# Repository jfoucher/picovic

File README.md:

# PICOVIC

This is a Commodore Vic-20 emulator for the [Raspberry Pi Pico](https://www.raspberrypi.org/products/raspberry-pi-pico/)

Most of the 6502 emulation code is from [fake6502](http://rubbermallet.org/fake6502.c).

A PS/2 keyboard can be plugged in to the pico according to [the schematic](hardware/picovic.pdf) and is used as an input device.

VGA output is based on the scanvideo code from [pico-extra](https://github.com/raspberrypi/pico-extras/tree/master/src/common/pico_scanvideo)

The emulation is extremely basic and for example the VIAs are only emulated so that the cursor works in BASIC. The VIC chip only has the most simple functionality, in the interest of speed and laziness. However since for the time being the emulated speed is higher than the original VIC-20, more functionality will be added in the future.

[Running BASIC video](basic.mp4)

## Hardware

I designed a PCB to go with it. You can check out the hardware folder to get the source, or [download the schematic](https://gitlab.com/jfoucher/picovic/-/jobs/artifacts/master/raw/hardware/Fabrication/Schematic.pdf?job=sch_outputs) and [gerber files](https://gitlab.com/jfoucher/picovic/-/jobs/artifacts/master/raw/hardware/Fabrication/gerbers.zip?job=pcb_outputs).

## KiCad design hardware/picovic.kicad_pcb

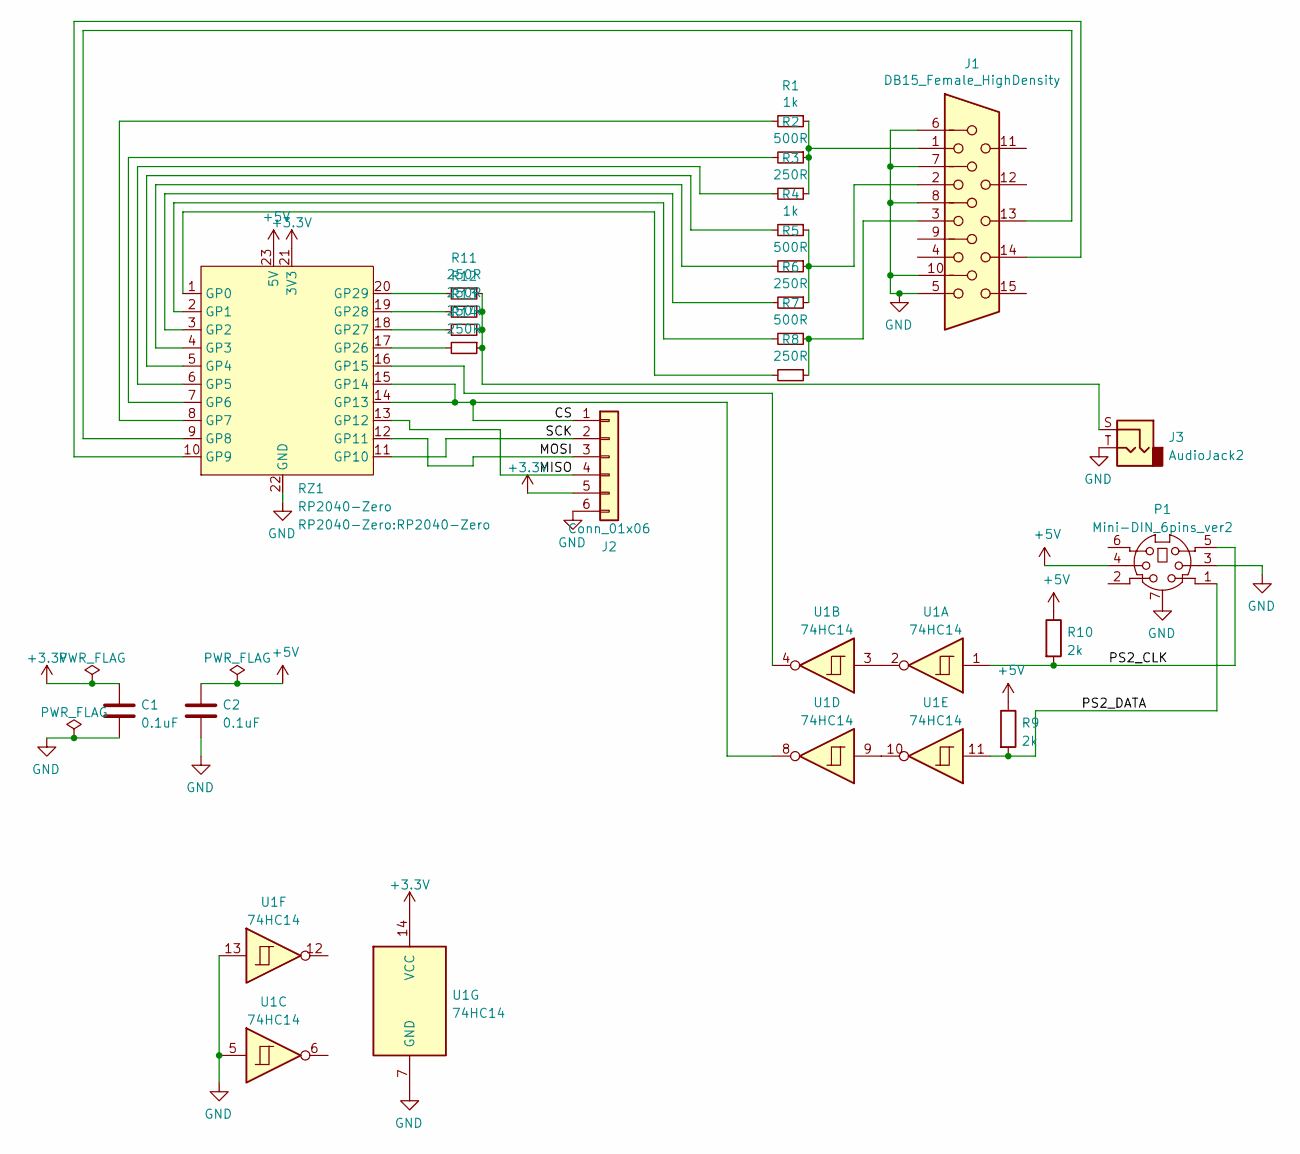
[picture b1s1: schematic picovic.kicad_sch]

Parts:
C1, C2: 0.1uF; C_Disc_D5.0mm_W2.5mm_P5.00mm
J1: DB15_Female_HighDensity; DSUB-15-HD_Female_Horizontal_P2.29x1.98mm_EdgePinOffset3.03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
J2: Conn_01x06; PinSocket_1x06_P2.54mm_Horizontal
J3: AudioJack2
P1: Mini-DIN_6pins_ver2; Connector_Mini-DIN_Female_6Pin_2rows
R1, R4: 1k; R_Axial_DIN0207_L6.3mm_D2.5mm_P7.62mm_Horizontal
R2, R5, R7: 500R; R_Axial_DIN0207_L6.3mm_D2.5mm_P7.62mm_Horizontal
R3, R6, R8, R11, R12, R13, R14: 250R; R_Axial_DIN0207_L6.3mm_D2.5mm_P7.62mm_Horizontal
R9, R10: 2k; R_Axial_DIN0207_L6.3mm_D2.5mm_P7.62mm_Horizontal
RZ1: RP2040-Zero
U1: 74HC14; DIP-14_W7.62mm_Socket

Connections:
+3.3V: C1.1, J2.5, RZ1.21 (3V3), U1.14 (VCC)
+5V: C2.1, P1.4, R9.1, R10.1, RZ1.23 (5V)
/CS: J2.1, RZ1.14 (GP13), RZ1.15 (GP14), U1.8
/MISO: J2.4, RZ1.13 (GP12)
/MOSI: J2.3, RZ1.12 (GP11)
/PS2_CLK: P1.5, R10.2, U1.1
/PS2_DATA: P1.1, R9.2, U1.11
/SCK: J2.2, RZ1.11 (GP10)
GND: C1.2, C2.2, J1.5, J1.6, J1.7, J1.8, J1.10, J2.6, J3.T, P1.3, P1.7 (Shell), RZ1.22 (GND), U1.5, U1.7 (GND), U1.13
unnamed: J1.1, R1.1, R2.1, R3.1
unnamed: J1.2, R4.1, R5.1, R6.1
unnamed: J1.3, R7.1, R8.1
unnamed: J1.13, RZ1.9 (GP8)
unnamed: J1.14, RZ1.10 (GP9)
unnamed: J3.S, R11.1, R12.1, R13.1, R14.1
unnamed: R3.2, RZ1.6 (GP5)
unnamed: R4.2, RZ1.5 (GP4)
unnamed: R5.2, RZ1.4 (GP3)
unnamed: R6.2, RZ1.3 (GP2)
unnamed: R7.2, RZ1.2 (GP1)
unnamed: R8.2, RZ1.1 (GP0)
unnamed: R2.2, RZ1.7 (GP6)
unnamed: R1.2, RZ1.8 (GP7)
unnamed: RZ1.16 (GP15), U1.4
unnamed: R14.2, RZ1.17 (GP26)
unnamed: R13.2, RZ1.18 (GP27)
unnamed: R12.2, RZ1.19 (GP28)
unnamed: R11.2, RZ1.20 (GP29)
unnamed: U1.2, U1.3
unnamed: U1.9, U1.10

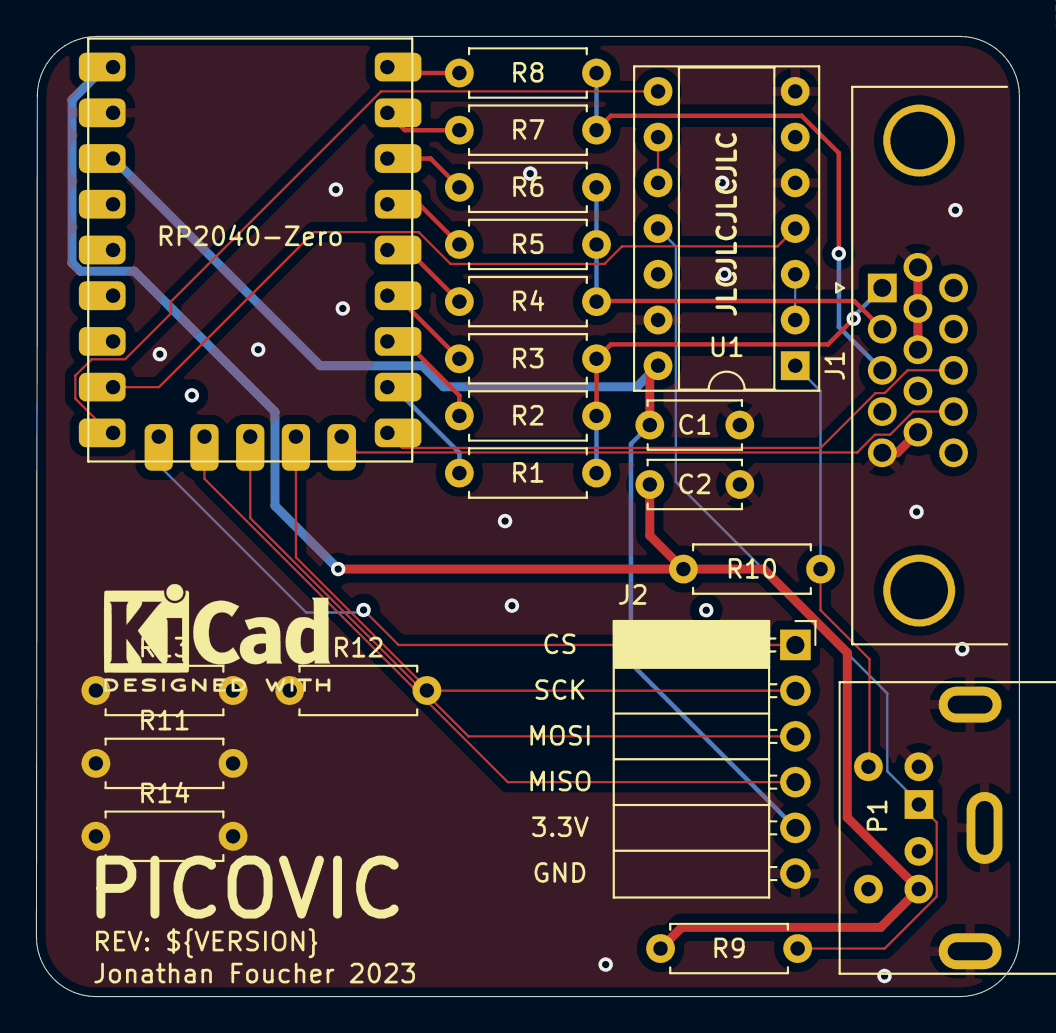
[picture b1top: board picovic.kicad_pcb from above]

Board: 2 copper layers, 54.6 x 53.3 mm, 21 parts (0 on the bottom side), 30 nets.

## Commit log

2021-07-08 vic-20
2021-07-13 only use 8 GPIO for video colors
2021-07-24 BRK fix
2021-07-24 Add links to issues
2021-07-24 can read via
2021-07-25 timer still not working
2021-07-26 more testing
2021-07-31 standalone cmake build
2021-08-04 fix multiple definition errors
2021-08-07 [WIP]
2021-08-08 Replace assembly version with simple C version of 6502 emulator
2021-08-08 Add ps/2 keyboard handling
2021-08-08 Use vblank instead of timer to generate interrupts.
2021-08-08 use time_critical macro
2021-08-12 reorganize + add schematic
2021-08-13 better videos
2021-08-13 update schematic
2021-08-13 reduce gif size
2021-08-13 cleanup
2021-08-13 Try to make delete key work
2021-08-13 Add debug launch option
2021-08-14 comments
2021-08-14 Make backspace work as delete key
2021-08-15 Can read data from SPI SD card
2021-08-17 Can read d64 image from SD card
2021-08-17 remove bits of test code
2021-08-17 starting to be able to load something.
2023-01-09 Change base pin + add kibot
2023-01-10 Fix violations
2023-01-10 remove kicad 5 files
2023-01-10 correct dir
2023-01-10 artifacts paths
2023-01-12 Only run on tags
2023-01-12 Add download links + image
2023-01-12 Set variables
2023-01-12 Fix ERC
2023-01-12 Fix readme
2023-01-12 remove hard coded strings + use smaller image for deploy
2023-01-12 Maybe fix variables ?
2023-01-12 do not skip all preflightrs
2023-02-09 Fix i2c pins order
2023-10-23 Create LICENSE
